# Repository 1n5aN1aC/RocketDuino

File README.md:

# RocketDuino
This is an Arduino Board designed for use in High-Powered model rockets.

(Picture Goes Here)

<h1>Features</h1>

 - Parachute Deployment:  Dual parachute deployment via high-power mosfets to route raw battery current directly through the ignitors.  (Designed for 9v)
 - GPS Tracking: On-board GPS used to verify hight measurements, get speed readouts, and know the location of the rocket.
 - Telemetry: LoRa telemetry transmission with a maximum range of over 8km.  This is used to relay location and height data to a ground control station to ease finding the rocket after parachute deployment.

<h1>Hardware</h1>

 - MCU: Early versions (which were flown successfully) used a wemos D1 mini.  However, the current version uses a Teensy LC as the main microcontroller.  This change was made primarily to take advantage of the multiple hardware serial ports on the Teensy line.
 - GPS:  Works with any Serial GPS device that outputs classic NMEA messages, (GPGGA, etc) does NOT currently support the newer GNGGA messages.  The PCB is designed to directly mount a uBlox NEO-M6N module.  (Note that the config needs to be changes to output GPGGA, etc)
 - Barometer:  A BMP280 is used for more accurate real-time elevation measurement.  Note that the Teensy is NOT 5v compliant, so you need the 3.3v BMP280 board.
 - Telemetry:  Data Transmission is done using a E32-433T30D 1W LoRa trasmitter, but any data transmitter with a serial interface should work, with only minor changes to the board.  (The PCB is designed to mount the module directly.)

<h3>The Board</h3>

Short Description coming soon.

[For Detailed PCB Information, click here](https://github.com/1n5aN1aC/RocketDuino/tree/master/PCB)

<h3>The Software</h3>

Short Description coming soon.

[For Detailed Arduino Information, click here](https://github.com/1n5aN1aC/RocketDuino/tree/master/Arduino)

<h3>The Results</h3>

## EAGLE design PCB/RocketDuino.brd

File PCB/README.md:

#PCB files
This is where the files for making the PCB are located.  We use Eagle as our development tool of choice.

##Features
Description Coming Soon!

##Design
Description Coming Soon!

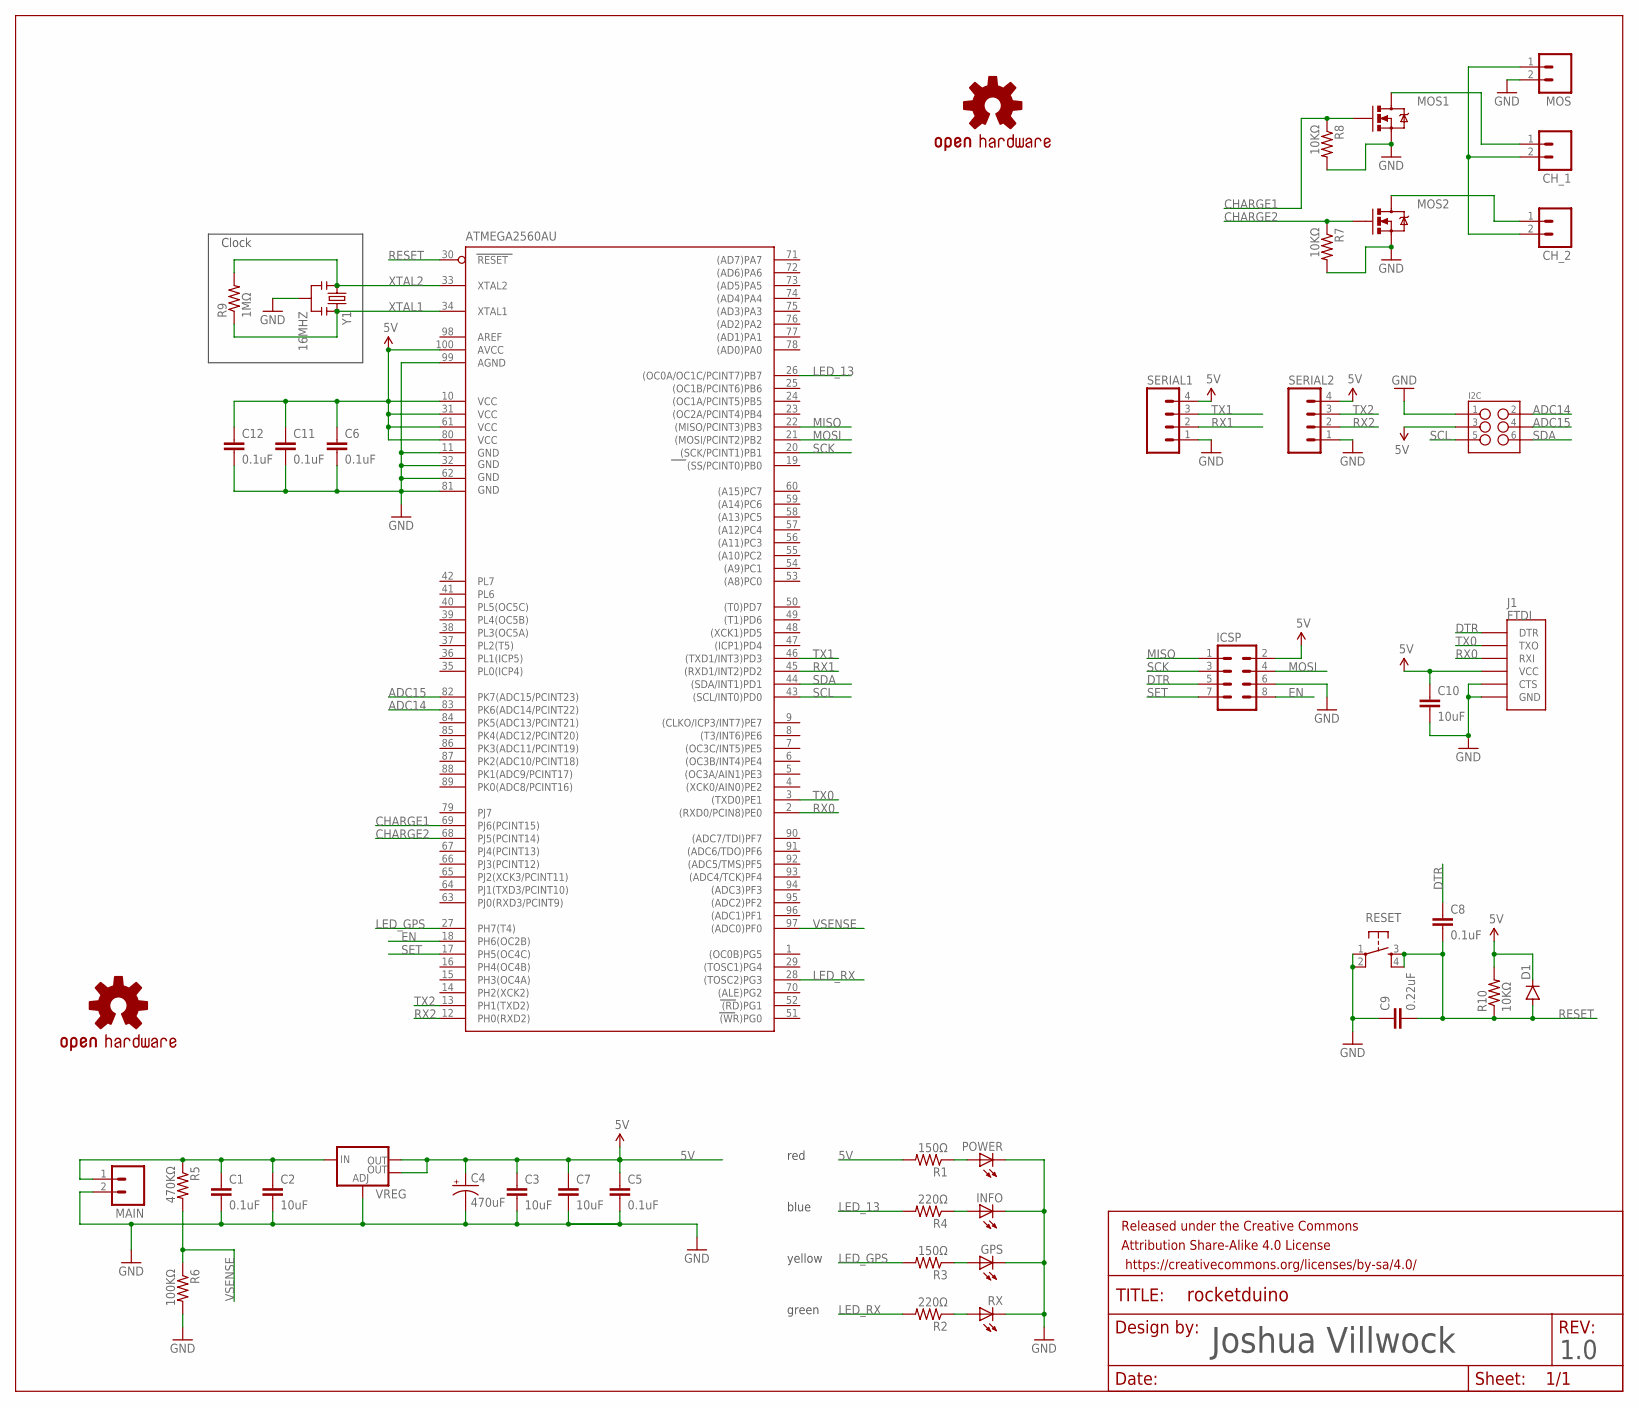
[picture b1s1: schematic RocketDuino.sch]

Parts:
ATMEGA2560AU: ATMEGA2560AU; TQFP100
C1, C5, C6, C8, C11, C12: 0.1uF; 1206
C2, C3, C7, C10: 10uF; 1206
C4: 470uF; CPOL-RADIAL-100UF-25V
C9: 0.22uF; 1206
CH_1, CH_2: M02LOCK_LONGPADS; 1X02_LOCK_LONGPADS
D1: DIODESMA-ALT; SMA-DIODE_ALT
FRAME1: FRAME-LEDGER; CREATIVE_COMMONS
GPS: LEDSML0805; SML0805
I2C: M03X2FEMALE; 2X3
ICSP: M04X2; 2X4
INFO: LEDSML0805; SML0805
J1: FTDI; FTDI_DEVICE_SIDE
LOGO1, LOGO2: OSHW-LOGOM; OSHW-LOGO-M
MAIN: M02LOCK_LONGPADS; 1X02_LOCK_LONGPADS
MOS: M02LOCK_LONGPADS; 1X02_LOCK_LONGPADS
MOS1, MOS2: MOSFET-NCHANNELFQP30N06L; TO220V
POWER: LEDSML0805; SML0805
R1, R3: 150Ω; 1206
R2, R4: 220Ω; 1206
R5: 470KΩ; 1206
R6: 100KΩ; 1206
R7, R8, R10: 10KΩ; 1206
R9: 1MΩ; 1206
RESET: SWITCH_SPST_4_PINSQUARE; TACTILE-SWITCH-SMD
RX: LEDSML0805; SML0805
SERIAL1, SERIAL2: M04POLAR; MOLEX-1X4
VREG: V_REG_LM1117SOT223; SOT223
Y1: 16MHZ; RESONATOR-SMD

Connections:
5V: ATMEGA2560AU.10 (VCC), ATMEGA2560AU.31 (VCC1), ATMEGA2560AU.61 (VCC2), ATMEGA2560AU.80 (VCC3), ATMEGA2560AU.100 (AVCC), C3.1, C4.1 (+), C5.1, C6.1, C7.1, C10.1, C11.1, C12.1, D1.C, I2C.3, ICSP.2, J1.P$4 (VCC), R1.2, R10.2, SERIAL1.4, SERIAL2.4, VREG.2 (OUT), VREG.4 (OUT)
ADC14: ATMEGA2560AU.83 (PK6(ADC14/PCINT22)), I2C.2
ADC15: ATMEGA2560AU.82 (PK7(ADC15/PCINT23)), I2C.4
CHARGE1: ATMEGA2560AU.69 (PJ6(PCINT15)), MOS1.1 (G), R8.1
CHARGE2: ATMEGA2560AU.68 (PJ5(PCINT14)), MOS2.1 (G), R7.1
DTR: C8.1, ICSP.5, J1.P$1 (DTR)
EN: ATMEGA2560AU.18 (PH6(OC2B)), ICSP.8
GND: ATMEGA2560AU.11 (GND), ATMEGA2560AU.32 (GND1), ATMEGA2560AU.62 (GND2), ATMEGA2560AU.81 (GND3), ATMEGA2560AU.99 (AGND), C1.2, C2.2, C3.2, C4.2 (-), C5.2, C6.2, C7.2, C9.1, C10.2, C11.2, C12.2, GPS.C, I2C.1, ICSP.6, INFO.C, J1.P$5 (CTS), J1.P$6 (GND), MAIN.2, MOS.2, MOS1.3 (S), MOS2.3 (S), POWER.C, R6.2, R7.2, R8.2, RESET.1, RESET.2, RX.C, SERIAL1.1, SERIAL2.1, VREG.1 (ADJ), Y1.2
LED_13: ATMEGA2560AU.26 ((OC0A/OC1C/PCINT7)PB7), R4.2
LED_GPS: ATMEGA2560AU.27 (PH7(T4)), R3.2
LED_RX: ATMEGA2560AU.28 ((TOSC2)PG3), R2.2
MISO: ATMEGA2560AU.22 ((MISO/PCINT3)PB3), ICSP.1
MOS1: CH_1.1, MOS1.2 (D)
MOS2: CH_2.1, MOS2.2 (D)
MOSI: ATMEGA2560AU.21 ((MOSI/PCINT2)PB2), ICSP.4
unnamed: GPS.A, R3.1
unnamed: POWER.A, R1.1
unnamed: INFO.A, R4.1
unnamed: R2.1, RX.A
RESET: ATMEGA2560AU.30 (RESET), C8.2, C9.2, D1.A, R10.1, RESET.3, RESET.4
RX0: ATMEGA2560AU.2 ((RXD0/PCIN8)PE0), J1.P$3 (RXI)
RX1: ATMEGA2560AU.45 ((RXD1/INT2)PD2), SERIAL1.2
RX2: ATMEGA2560AU.12 (PH0(RXD2)), SERIAL2.2
SCK: ATMEGA2560AU.20 ((SCK/PCINT1)PB1), ICSP.3
SCL: ATMEGA2560AU.43 ((SCL/INT0)PD0), I2C.5
SDA: ATMEGA2560AU.44 ((SDA/INT1)PD1), I2C.6
SET: ATMEGA2560AU.17 (PH5(OC4C)), ICSP.7
TX0: ATMEGA2560AU.3 ((TXD0)PE1), J1.P$2 (TXO)
TX1: ATMEGA2560AU.46 ((TXD1/INT3)PD3), SERIAL1.3
TX2: ATMEGA2560AU.13 (PH1(TXD2)), SERIAL2.3
VIN: C1.1, C2.1, MAIN.1, R5.1, VREG.3 (IN)
VIN_MOS: CH_1.2, CH_2.2, MOS.1
VSENSE: ATMEGA2560AU.97 ((ADC0)PF0), R5.2, R6.1
XTAL1: ATMEGA2560AU.34 (XTAL1), R9.1, Y1.3
XTAL2: ATMEGA2560AU.33 (XTAL2), R9.2, Y1.1

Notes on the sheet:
Clock
green
yellow
blue
red
Joshua Villwock
1.0

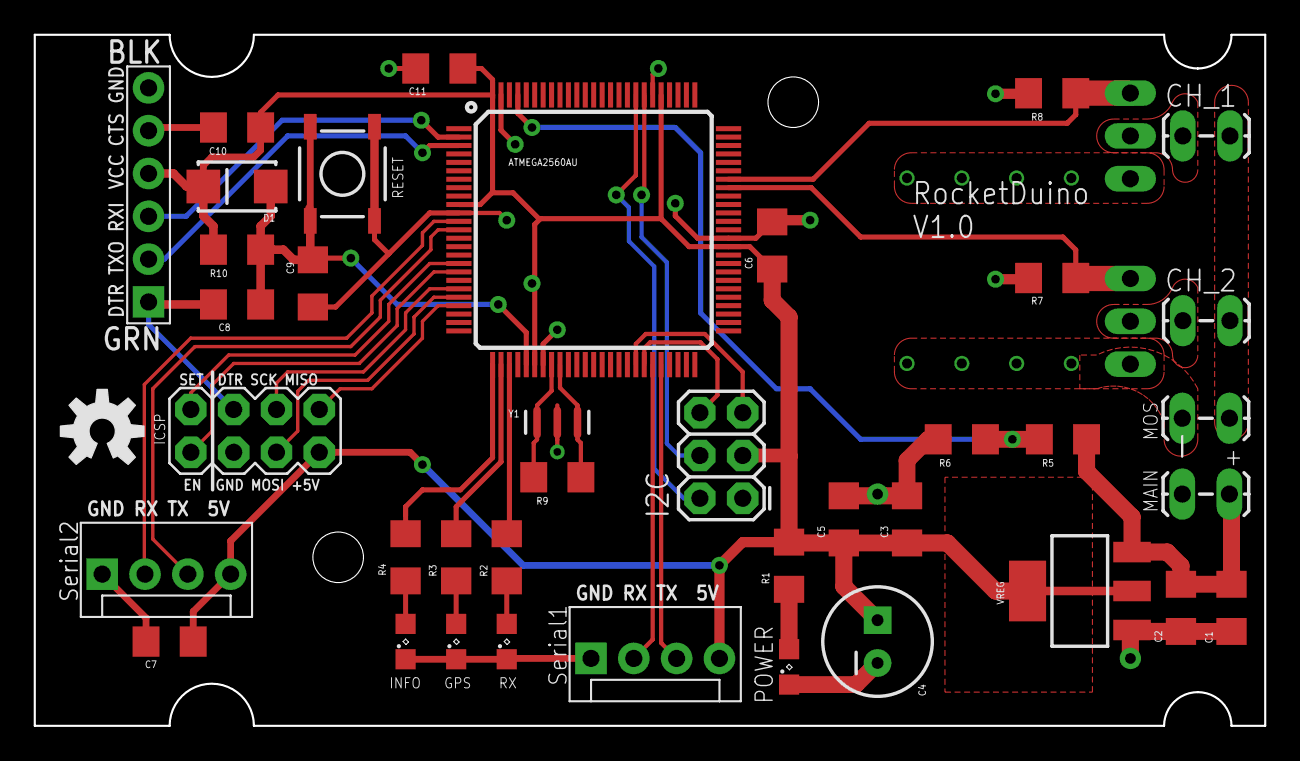
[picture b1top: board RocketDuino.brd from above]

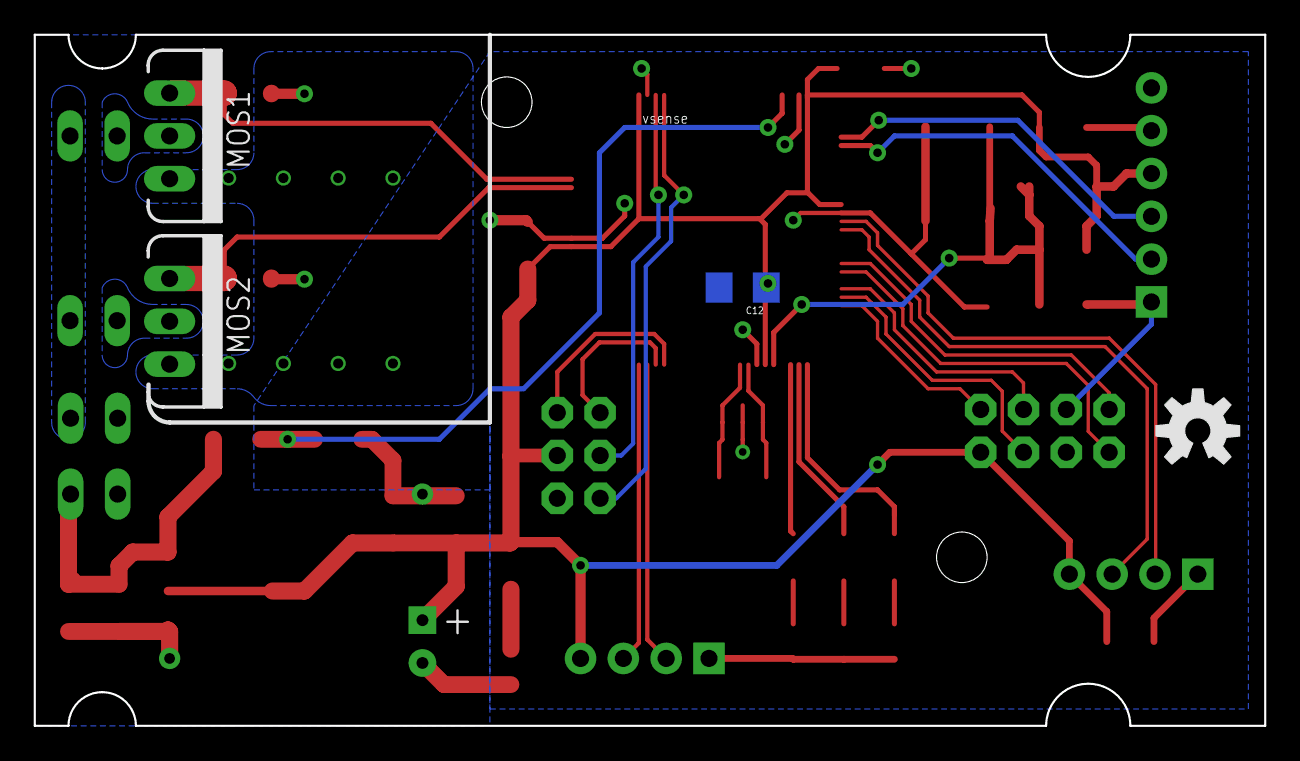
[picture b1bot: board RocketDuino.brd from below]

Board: 2 copper layers, 73.0 x 41.0 mm, 45 parts (4 on the bottom side), 35 nets.

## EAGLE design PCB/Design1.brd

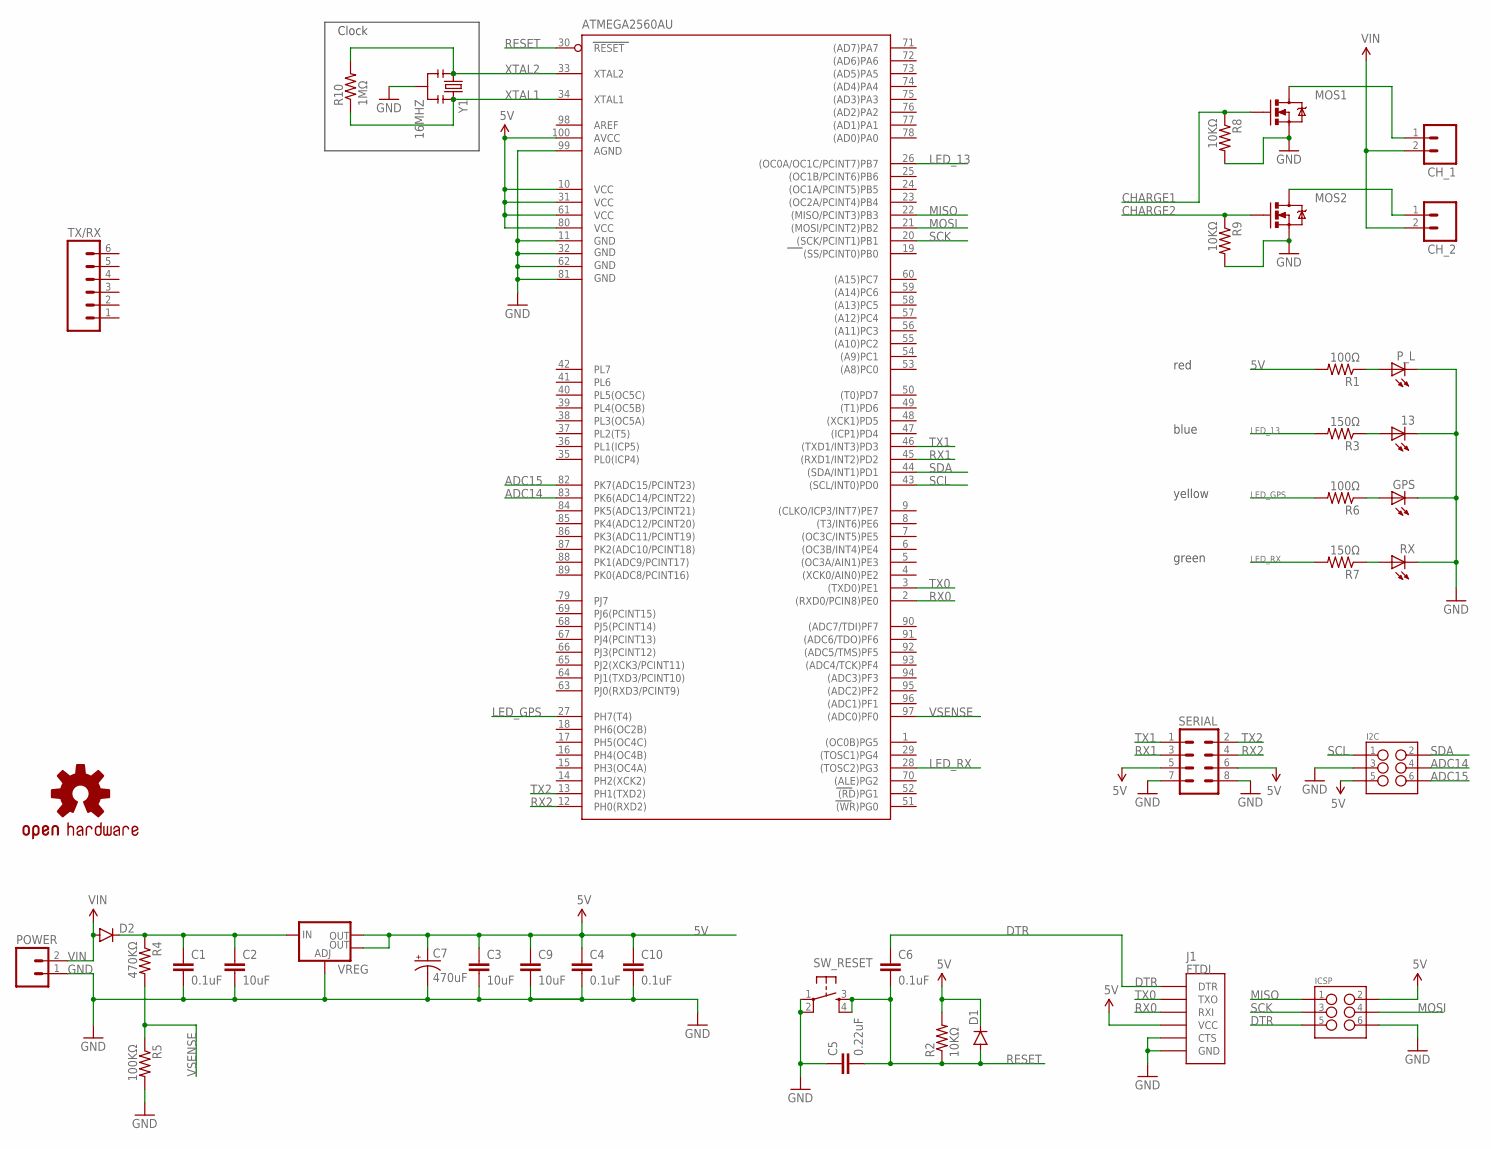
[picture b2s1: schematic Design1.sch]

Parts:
13: LEDSML0805; SML0805
ATMEGA2560AU: ATMEGA2560AU; TQFP100
C1, C4, C6, C10: 0.1uF; 1206
C2, C3, C9: 10uF; 1206
C5: 0.22uF; 1206
C7: 470uF; CPOL-RADIAL-100UF-25V
CH_1, CH_2: M02LOCK_LONGPADS; 1X02_LOCK_LONGPADS
D1, D2: DIODESMA-ALT; SMA-DIODE_ALT
GPS: LEDSML0805; SML0805
I2C: M03X2FEMALE_SMD; 2X3_SMD
ICSP: M03X2FEMALE_SMD; 2X3_SMD
J1: FTDI; FTDI_DEVICE_SIDE
LOGO1: OSHW-LOGOM; OSHW-LOGO-M
MOS1, MOS2: MOSFET-NCHANNELFQP30N06L; TO220V
POWER: M02LOCK_LONGPADS; 1X02_LOCK_LONGPADS
P_L: LEDSML0805; SML0805
R1, R6: 100Ω; 1206
R2, R8, R9: 10KΩ; 1206
R3, R7: 150Ω; 1206
R4: 470KΩ; 1206
R5: 100KΩ; 1206
R10: 1MΩ; 1206
RX: LEDSML0805; SML0805
SERIAL: M04X2; 2X4
SW_RESET: SWITCH_SPST_4_PINSQUARE; TACTILE-SWITCH-SMD
TX/RX: M06SILK_FEMALE_PTH; 1X06
VREG: V_REG_LM1117SOT223; SOT223
Y1: 16MHZ; RESONATOR-SMD

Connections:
5V: ATMEGA2560AU.10 (VCC), ATMEGA2560AU.31 (VCC1), ATMEGA2560AU.61 (VCC2), ATMEGA2560AU.80 (VCC3), ATMEGA2560AU.100 (AVCC), C3.1, C4.1, C7.1 (+), C9.1, C10.1, D1.C, I2C.5, ICSP.2, J1.P$4 (VCC), R1.2, R2.2, SERIAL.5, SERIAL.6, VREG.2 (OUT), VREG.4 (OUT)
ADC14: ATMEGA2560AU.83 (PK6(ADC14/PCINT22)), I2C.4
ADC15: ATMEGA2560AU.82 (PK7(ADC15/PCINT23)), I2C.6
CHARGE1: MOS1.1 (G), R8.1
CHARGE2: MOS2.1 (G), R9.1
DTR: C6.1, ICSP.5, J1.P$1 (DTR)
GND: 13.C, ATMEGA2560AU.11 (GND), ATMEGA2560AU.32 (GND1), ATMEGA2560AU.62 (GND2), ATMEGA2560AU.81 (GND3), ATMEGA2560AU.99 (AGND), C1.2, C2.2, C3.2, C4.2, C5.1, C7.2 (-), C9.2, C10.2, GPS.C, I2C.3, ICSP.6, J1.P$5 (CTS), J1.P$6 (GND), MOS1.3 (S), MOS2.3 (S), POWER.1, P_L.C, R5.2, R8.2, R9.2, RX.C, SERIAL.7, SERIAL.8, SW_RESET.1, SW_RESET.2, VREG.1 (ADJ), Y1.2
LED_13: ATMEGA2560AU.26 ((OC0A/OC1C/PCINT7)PB7), R3.2
LED_GPS: ATMEGA2560AU.27 (PH7(T4)), R6.2
LED_RX: ATMEGA2560AU.28 ((TOSC2)PG3), R7.2
MISO: ATMEGA2560AU.22 ((MISO/PCINT3)PB3), ICSP.1
MOS1: CH_1.1, MOS1.2 (D)
MOS2: CH_2.1, MOS2.2 (D)
MOSI: ATMEGA2560AU.21 ((MOSI/PCINT2)PB2), ICSP.4
unnamed: GPS.A, R6.1
unnamed: P_L.A, R1.1
unnamed: 13.A, R3.1
unnamed: R7.1, RX.A
RESET: ATMEGA2560AU.30 (RESET), C5.2, C6.2, D1.A, R2.1, SW_RESET.3, SW_RESET.4
RX0: ATMEGA2560AU.2 ((RXD0/PCIN8)PE0), J1.P$3 (RXI)
RX1: ATMEGA2560AU.45 ((RXD1/INT2)PD2), SERIAL.3
RX2: ATMEGA2560AU.12 (PH0(RXD2)), SERIAL.4
SCK: ATMEGA2560AU.20 ((SCK/PCINT1)PB1), ICSP.3
SCL: ATMEGA2560AU.43 ((SCL/INT0)PD0), I2C.1
SDA: ATMEGA2560AU.44 ((SDA/INT1)PD1), I2C.2
TX0: ATMEGA2560AU.3 ((TXD0)PE1), J1.P$2 (TXO)
TX1: ATMEGA2560AU.46 ((TXD1/INT3)PD3), SERIAL.1
TX2: ATMEGA2560AU.13 (PH1(TXD2)), SERIAL.2
VIN: CH_1.2, CH_2.2, D2.A, POWER.2
VIN_RECTIFIED: C1.1, C2.1, D2.C, R4.1, VREG.3 (IN)
VSENSE: ATMEGA2560AU.97 ((ADC0)PF0), R4.2, R5.1
XTAL1: ATMEGA2560AU.34 (XTAL1), R10.1, Y1.3
XTAL2: ATMEGA2560AU.33 (XTAL2), R10.2, Y1.1

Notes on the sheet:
Clock
green
yellow
blue
red

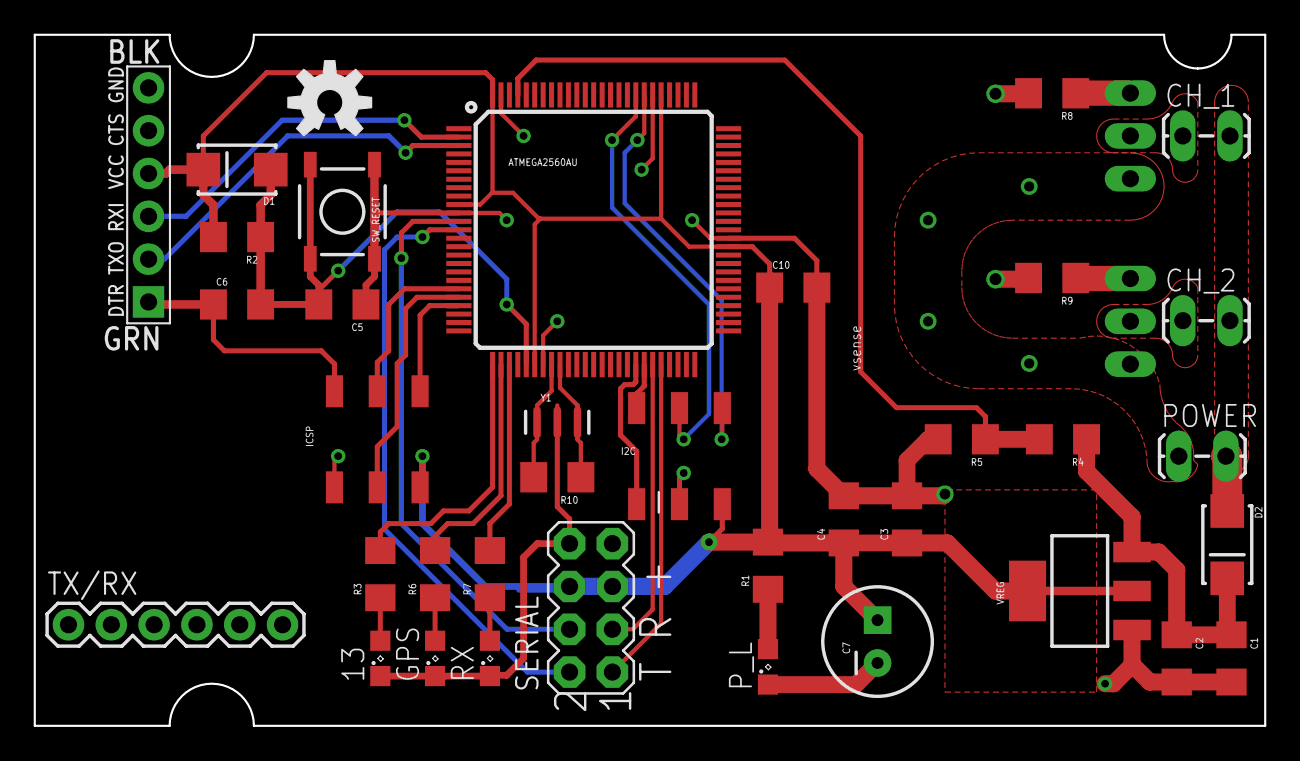
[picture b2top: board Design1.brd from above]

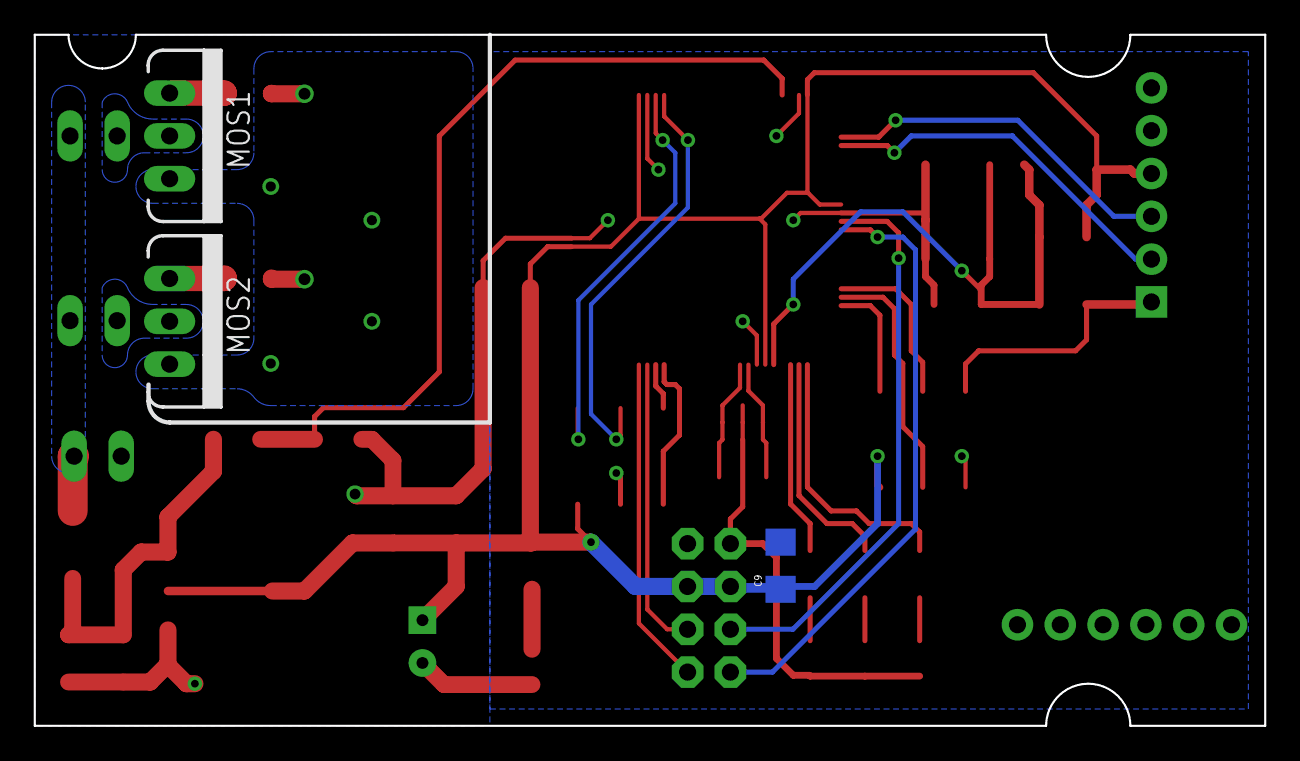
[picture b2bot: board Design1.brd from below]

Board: 2 copper layers, 73.0 x 41.0 mm, 40 parts (3 on the bottom side), 33 nets.

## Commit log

2016-07-07 Add License File
    Creative Commons Attribution-ShareAlike 4.0 International (CC BY-SA 4.0)
2016-07-07 Create Initial readme
2016-07-07 Add information to readme
2016-07-07 clean up readme
2016-07-08 Add the gitignore for Eagle
2016-07-08 Add Eagle PCB Files
2016-07-08 Add original Arduino code
2016-07-08 Add readme page for PCB
2016-07-08 ..move to correct location
2016-07-08 add readme for Arduino code
2016-07-08 grammer fix
2016-07-08 update main readme to point to specific ones
2016-07-08 Update new Schematic
2016-07-08 Update new Board
2016-07-09 Added battery voltage sensing; Clean up of code
    Also had to rename file to get the Arduino suite to edit it :/
2016-07-09 last nights' Schematic updates
2016-07-10 Add ICSP & Organize LEDs
2016-07-10 Ad LEDS, begin work on MOSFETs
2016-07-10 Place mosfets
2016-07-10 switch to SMT 5v regulators
2016-07-11 Remove 3.3v; clean up Ground near MOSFETS
2016-07-11 Remove 3.3v; clean up Ground near MOSFETS #2
2016-07-12 Move componets to (hopefully) final location
2016-07-12 DTR fix
2016-07-12 Finalize part locations; Route most of the traces
2016-07-12 Finalize part locations; Route most of the traces 2
2016-07-13 Finish routing traces
2016-07-13 minor fixes
2016-07-13 Finish routing. Minor changes
2016-07-13 Whoops. fix that.
2016-07-13 Finish routing. Minor changes 2
2016-07-14 Add support for ground station pings
2016-07-14 Fixes & documentation
2016-07-14 Minor Speed Optimizations
2016-07-14 Removed 1x 5v regulator; relabeling
2016-07-14 Labeling Cleanup
2016-07-15 Add control for the Charges. Whoops.
2016-07-15 Add control for the Charges. Whoops. (2)
2016-07-15 Organize the Schematic Nicely
2016-07-16 Fix part of ground plane
2016-07-18 Very minor board movements
2016-07-20 Clean schematic; Shift Board componets
2016-07-20 Clean schematic; Shift Board componets 2
2016-07-21 tired
2016-07-22 Clean up all Silkscreen Indicators
2016-07-22 Made C4 Explosive
2016-07-24 Seperated Serial 1 & 2
2016-07-24 Add Labels for Serial
2016-07-24 Add Labels (2)
2016-07-24 Revert "Add Labels (2)"
    This reverts commit 649e5ca491e825c42b75eb8464ca0d71b423613b.
2016-07-24 Revert "Revert "Add Labels (2)""
    This reverts commit 35d22b4ccda85a27ff9208a5b721f9a8abebe91e.
2016-07-24 New DRU settings
2016-07-25 Cleanups from Reddit post
2016-07-26 Non-SMT I2C connector
2016-07-26 Silkscreen Changes
    Also re-routed the Vsense wire
2016-07-26 Minor Labeling fix
2016-07-26 Minor Re-routes of traces
2016-07-27 Silkscreen changes
2016-07-27 add global variables for tracking
    Also removed VDOP. sorry.
2016-07-29 No more course data
2016-07-30 Framework for flight modes
2016-07-31 Add voltage averaging
2016-08-05 Move communications to seperate module
2016-08-05 Update flgiht info
2016-08-05 Tabs are better (2)
2016-08-07 Revert "Tabs are better (2)"
    This reverts commit 6dbf015bb0377da0e4a0b3b7260c7ab30771f142.
2021-10-22 ROCKETDUINO_VERSION "0.3.2"
2021-10-22 ROCKETDUINO_VERSION "0.3.2.1"
2021-10-22 ROCKETDUINO_VERSION "0.3.4"
2021-10-22 ROCKETDUINO_VERSION "0.4.0"
2021-10-22 ROCKETDUINO_VERSION "3.5.0"
2021-10-22 ROCKETDUINO_VERSION "3.7.0"
    I believe this is the version that flew on flights 1 & 2
2021-10-22 First change for switching to Teensy board
2021-10-22 Groundstation code for flights 1 & 2
2021-10-22 PCB version 3.7
2021-10-22 we don't actually support GNGGA et. all yet.
2021-10-22 Latest version of the Teensy-based board
2021-10-22 Final v4.0 pcb version
2022-02-04 Begin work on Code for PCB 4.2
    This is the move to teensy
2022-02-14 Board updates for v4.2
2022-07-20 begin of new version
2022-07-21 Only save when there are changes
2022-07-22 testing for lora live
2022-07-24 lora code working via aux pin
2022-07-24 rearange struct
2022-07-25 explicit casting
2022-08-16 new struct w/ checksum

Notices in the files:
parts and their libraries:
SparkFun-DigitalIC: Licensing: Creative Commons ShareAlike 4.0 International - https://creativecommons.org/licenses/by-sa/4.0
SparkFun-Aesthetics: Released under the Creative Commons Attribution Share-Alike 4.0 License
SparkFun-Aesthetics: https://creativecommons.org/licenses/by-sa/4.0
